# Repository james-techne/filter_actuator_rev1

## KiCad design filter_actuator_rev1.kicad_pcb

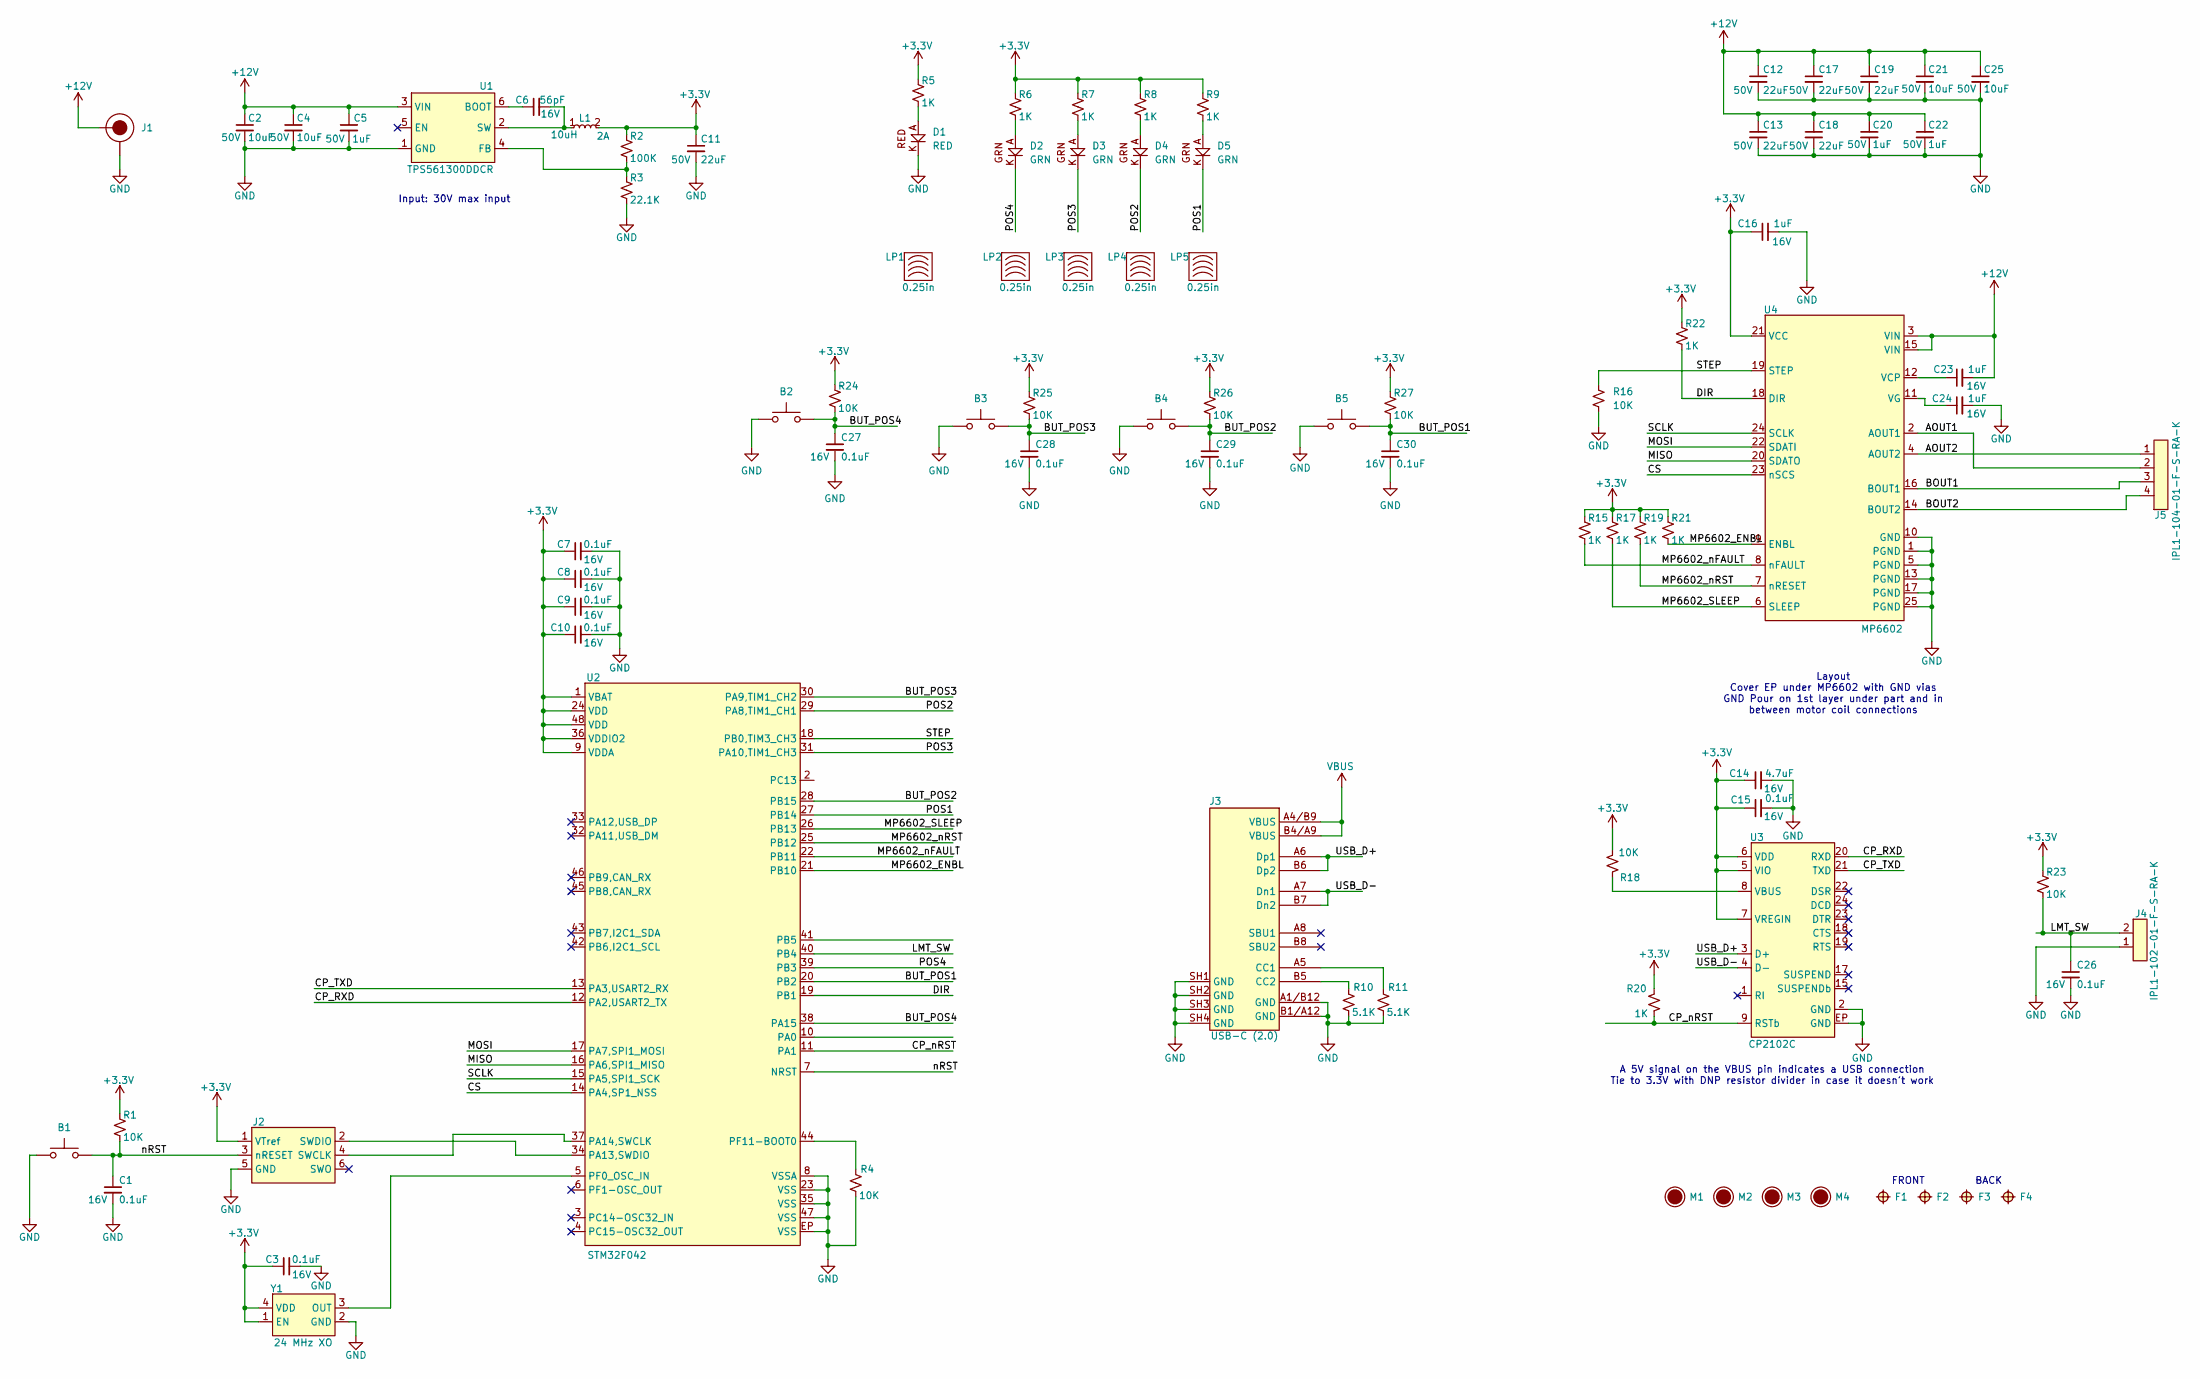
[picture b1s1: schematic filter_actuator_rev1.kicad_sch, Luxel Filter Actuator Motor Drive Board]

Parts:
B1: C&K_pushbutton; MPN PTS815SJM250SMTRLFS
B2, B3, B4, B5: B3FS-1032; MPN B3FS-1052
C1, C3, C7, C8, C9, C10, C15, C26, C27, C28, C29, C30: 0.1uF; C_0402_1005Metric; Voltage Rating 16V; MPN GRM155R61C104KA88D
C2, C4, C21, C25: 10uF; C_1206_3216Metric; Voltage Rating 50V; MPN GRT31CR61H106KE01K
C5: 1uF; C_0805_2012Metric; Voltage Rating 50V; MPN GCM21BR71H105KA03L
C6: 56pF; C_0402_1005Metric; Voltage Rating 16V; MPN KGM05ACG1C560KH
C11, C12, C13, C17, C18, C19: 22uF; C_1812_4532Metric; Voltage Rating 50V; MPN GMC43X7R226K50NT
C14: 4.7uF; C_0402_1005Metric; Voltage Rating 16V; MPN KGM05CR51C475MH
C16, C23, C24: 1uF; C_0402_1005Metric; Voltage Rating 16V; MPN CL05A105KO5NNNC
C20, C22: 1uF; C_0402_1005Metric; Voltage Rating 50V; MPN UMK105CBJ105MV-F
D1: RED; LIteOn_0603; MPN LTST-C191KRKT
D2, D3, D4, D5: GRN; LIteOn_0603; MPN LTST-C190KGKT
F1, F2, F3, F4: fiducial_1mm_2mm
J1: PJ-002AH_Power Barrel; MPN PJ-002AH
J2: JLink_needle_6pin; MPN N/A
J3: USB-C (2.0); SAMESKY_UJ20-C-H-G-SMT-2A-P16-TR; MPN UJ20-C-H-G-SMT-2A-P16-TR
J4: IPL1-102-01-F-S-RA-K; SAMTEC_IPL1-102-01-X-S-RA-K; MPN IPL1-106-01-F-S-RA-K
J5: IPL1-104-01-F-S-RA-K; SAMTEC_IPL1-104-01-X-S-RA-K; MPN IPL1-106-01-F-S-RA-K
L1: 10uH; IND_SRR6038-100Y; Rating 2A; MPN SRR6038-100Y
LP1, LP2, LP3, LP4, LP5: 0.25in; Dialight_515-1314-xxxx; MPN 515-1314-0250PF
M1, M2, M3, M4: M3_NPLATED_TH; MPN N/A
R1, R4, R16, R18, R23, R24, R25, R26, R27: 10K; R_0402_1005Metric; MPN RC0402FR-0710KP
R2: 100K; R_0402_1005Metric; MPN RC0402FR-07100KL
R3: 22.1K; R_0402_1005Metric; MPN RC0402FR-1322K1L
R5, R6, R7, R8, R9, R15, R17, R19, R20, R21, R22: 1K; R_0402_1005Metric; MPN RC0402FR-071KL
R10, R11: 5.1K; R_0402_1005Metric; MPN RC0402FR-075K1L
U1: TPS561300DDCR; ti_DDC0006A_SOT23; MPN TPS561300DDCR
U2: STM32F042; QFN50P700X700X60-49N; MPN STM32F042C6U6
U3: CP2102C; IC_QFN24_SIL; MPN CP2102C-A01-GQFN24R
U4: MP6602; QFN-25_MP6602_MNP; MPN MP6602GV-Z
Y1: 24 MHz XO; OSC_ECS-2333-480-BN-TR; MPN ECS-2333-240-BN-TR

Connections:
+3.3V: C3.1, C7.1, C8.1, C9.1, C10.1, C11.1, C14.1, C15.1, C16.1, J2.1 (VTref), L1.2, R1.1, R2.1, R5.1, R6.1, R7.1, R8.1, R9.1, R15.1, R17.1, R18.2, R19.1, R20.1, R21.1, R22.1, R23.1, R24.1, R25.1, R26.1, R27.1, U2.1 (VBAT), U2.9 (VDDA), U2.24 (VDD), U2.36 (VDDIO2), U2.48 (VDD), U3.5 (VIO), U3.6 (VDD), U3.7 (VREGIN), U4.21 (VCC), Y1.1 (EN), Y1.4 (VDD)
+12V: C2.1, C4.1, C5.1, C12.1, C13.1, C17.1, C18.1, C19.1, C20.1, C21.1, C22.1, C23.2, C25.1, J1.1 (V+), U1.3 (VIN), U4.3 (VIN), U4.15 (VIN)
/AOUT1: J5.2, U4.2 (AOUT1)
/AOUT2: J5.1, U4.4 (AOUT2)
/BOUT1: J5.3, U4.16 (BOUT1)
/BOUT2: J5.4, U4.14 (BOUT2)
/BUT_POS1: B5.4, C30.1, R27.2, U2.20 (PB2)
/BUT_POS2: B4.4, C29.1, R26.2, U2.28 (PB15)
/BUT_POS3: B3.4, C28.1, R25.2, U2.30 (PA9,TIM1_CH2)
/BUT_POS4: B2.4, C27.1, R24.2, U2.38 (PA15)
/CP_RXD: U2.12 (PA2,USART2_TX), U3.20 (RXD)
/CP_TXD: U2.13 (PA3,USART2_RX), U3.21 (TXD)
/CP_nRST: R20.2, U2.11 (PA1), U3.9 (RSTb)
/CS: U2.14 (PA4,SP1_NSS), U4.23 (nSCS)
/DIR: R22.2, U2.19 (PB1), U4.18 (DIR)
/LMT_SW: C26.1, J4.2, R23.2, U2.40 (PB4)
/MISO: U2.16 (PA6,SPI1_MISO), U4.20 (SDATO)
/MOSI: U2.17 (PA7,SPI1_MOSI), U4.22 (SDATI)
/MP6602_ENBL: R21.2, U2.21 (PB10), U4.9 (ENBL)
/MP6602_SLEEP: R17.2, U2.26 (PB13), U4.6 (SLEEP)
/MP6602_nFAULT: R15.2, U2.22 (PB11), U4.8 (nFAULT)
/MP6602_nRST: R19.2, U2.25 (PB12), U4.7 (nRESET)
/POS1: D5.K, U2.27 (PB14)
/POS2: D4.K, U2.29 (PA8,TIM1_CH1)
/POS3: D3.K, U2.31 (PA10,TIM1_CH3)
/POS4: D2.K, U2.39 (PB3)
/SCLK: U2.15 (PA5,SPI1_SCK), U4.24 (SCLK)
/STEP: R16.1, U2.18 (PB0,TIM3_CH3), U4.19 (STEP)
/USB_D+: J3.A6 (Dp1), J3.B6 (Dp2), U3.3 (D+)
/USB_D-: J3.A7 (Dn1), J3.B7 (Dn2), U3.4 (D-)
/nRST: B1.4, C1.1, J2.3 (nRESET), R1.2, U2.7 (NRST)
GND: B1.1, B1.2, B2.1, B2.2, B3.1, B3.2, B4.1, B4.2, B5.1, B5.2, C1.2, C2.2, C3.2, C4.2, C5.2, C7.2, C8.2, C9.2, C10.2, C11.2, C12.2, C13.2, C14.2, C15.2, C16.2, C17.2, C18.2, C19.2, C20.2, C21.2, C22.2, C24.2, C25.2, C26.2, C27.2, C28.2, C29.2, C30.2, D1.K, J1.2 (GND), J1.3 (GND), J2.5 (GND), J3.A1/B12 (GND), J3.B1/A12 (GND), J3.SH1 (GND), J3.SH2 (GND), J3.SH3 (GND), J3.SH4 (GND), J4.1, R3.2, R4.2, R10.2, R11.2, R16.2, U1.1 (GND), U2.8 (VSSA), U2.23 (VSS), U2.35 (VSS), U2.47 (VSS), U2.EP (VSS), U3.2 (GND), U3.EP (GND), U4.1 (PGND), U4.5 (PGND), U4.10 (GND), U4.13 (PGND), U4.17 (PGND), U4.25 (PGND), Y1.2 (GND)
unnamed: D1.A, R5.2
unnamed: D2.A, R6.2
unnamed: D3.A, R7.2
unnamed: D4.A, R8.2
unnamed: D5.A, R9.2
unnamed: J2.4 (SWCLK), U2.37 (PA14,SWCLK)
unnamed: J2.2 (SWDIO), U2.34 (PA13,SWDIO)
unnamed: J3.A5 (CC1), R11.1
unnamed: J3.B5 (CC2), R10.1
unnamed: C6.1, U1.6 (BOOT)
unnamed: R2.2, R3.1, U1.4 (FB)
unnamed: C6.2, L1.1, U1.2 (SW)
unnamed: U2.5 (PF0_OSC_IN), Y1.3 (OUT)
unnamed: R4.1, U2.44 (PF11-BOOT0)
unnamed: R18.1, U3.8 (VBUS)
unnamed: C23.1, U4.12 (VCP)
unnamed: C24.1, U4.11 (VG)
VBUS: J3.A4/B9 (VBUS), J3.B4/A9 (VBUS)

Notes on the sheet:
A 5V signal on the VBUS pin indicates a USB connection Tie to 3.3V with DNP resistor divider in case it doesn't work
Layout Cover EP under MP6602 with GND vias GND Pour on 1st layer under part and in between motor coil connections
Input: 30V max input
BACK
FRONT

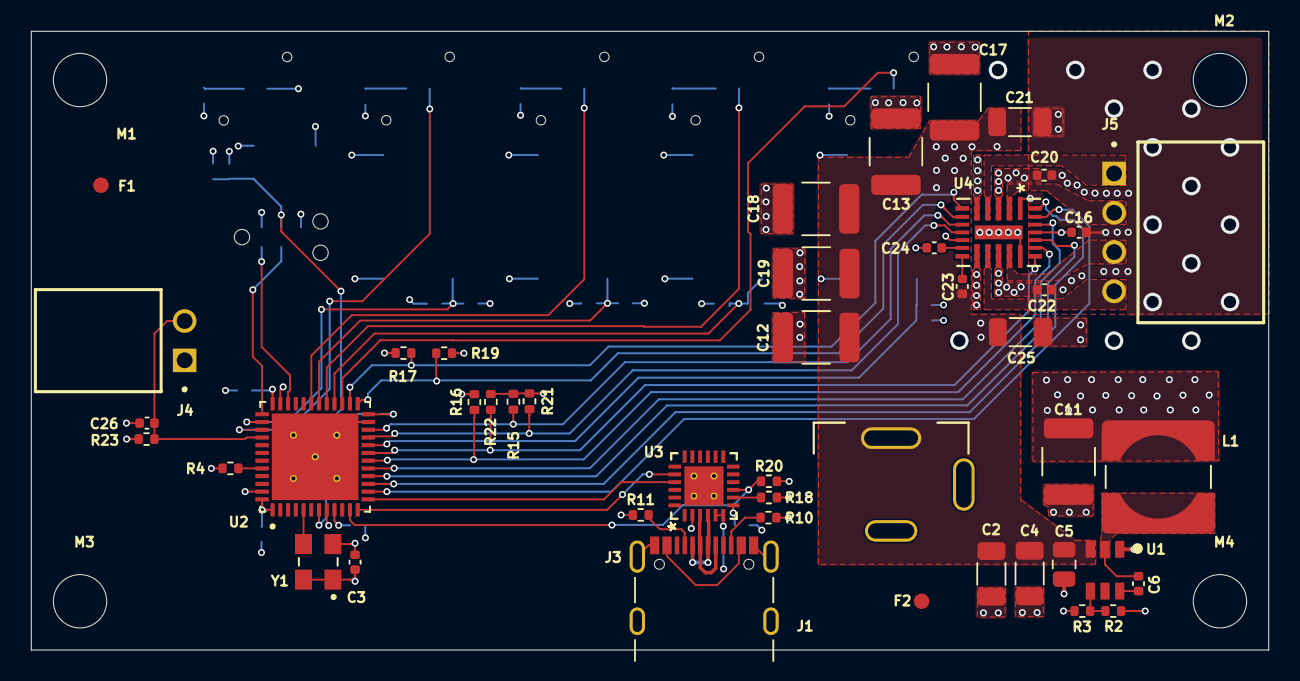
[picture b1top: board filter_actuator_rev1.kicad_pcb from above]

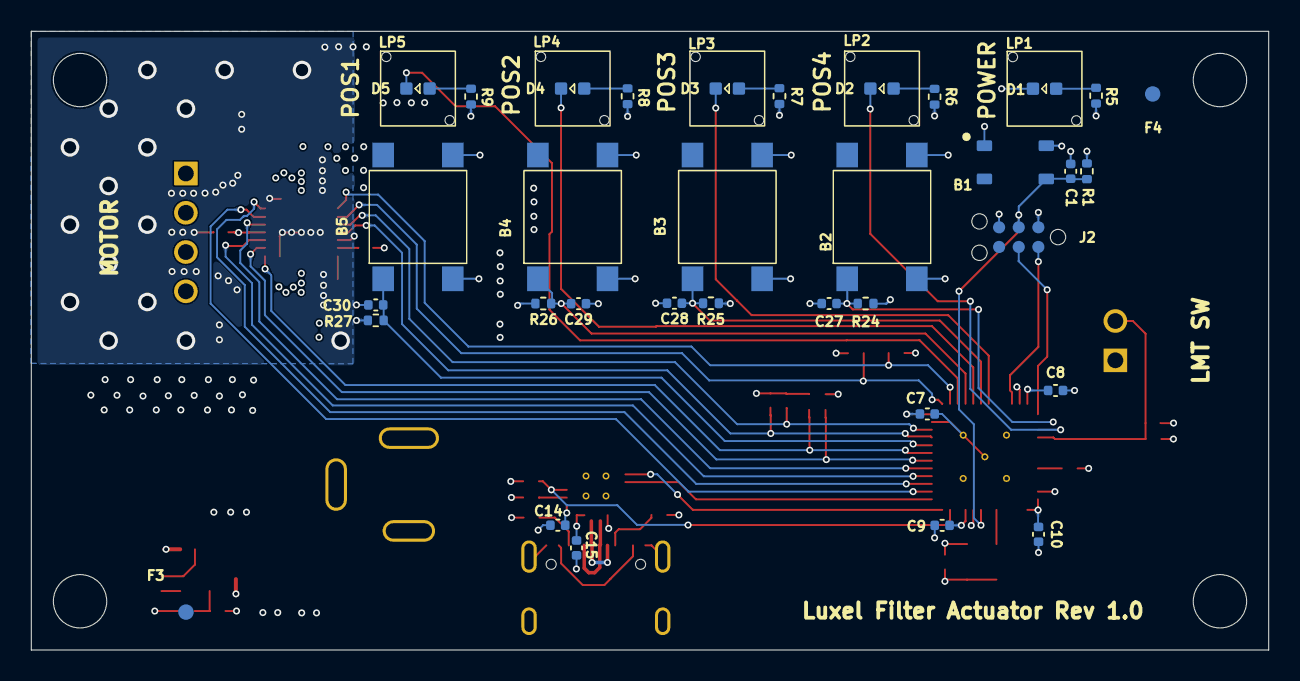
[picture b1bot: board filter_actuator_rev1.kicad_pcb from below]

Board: 4 copper layers, 80.0 x 40.0 mm, 88 parts (39 on the bottom side), 50 nets.
